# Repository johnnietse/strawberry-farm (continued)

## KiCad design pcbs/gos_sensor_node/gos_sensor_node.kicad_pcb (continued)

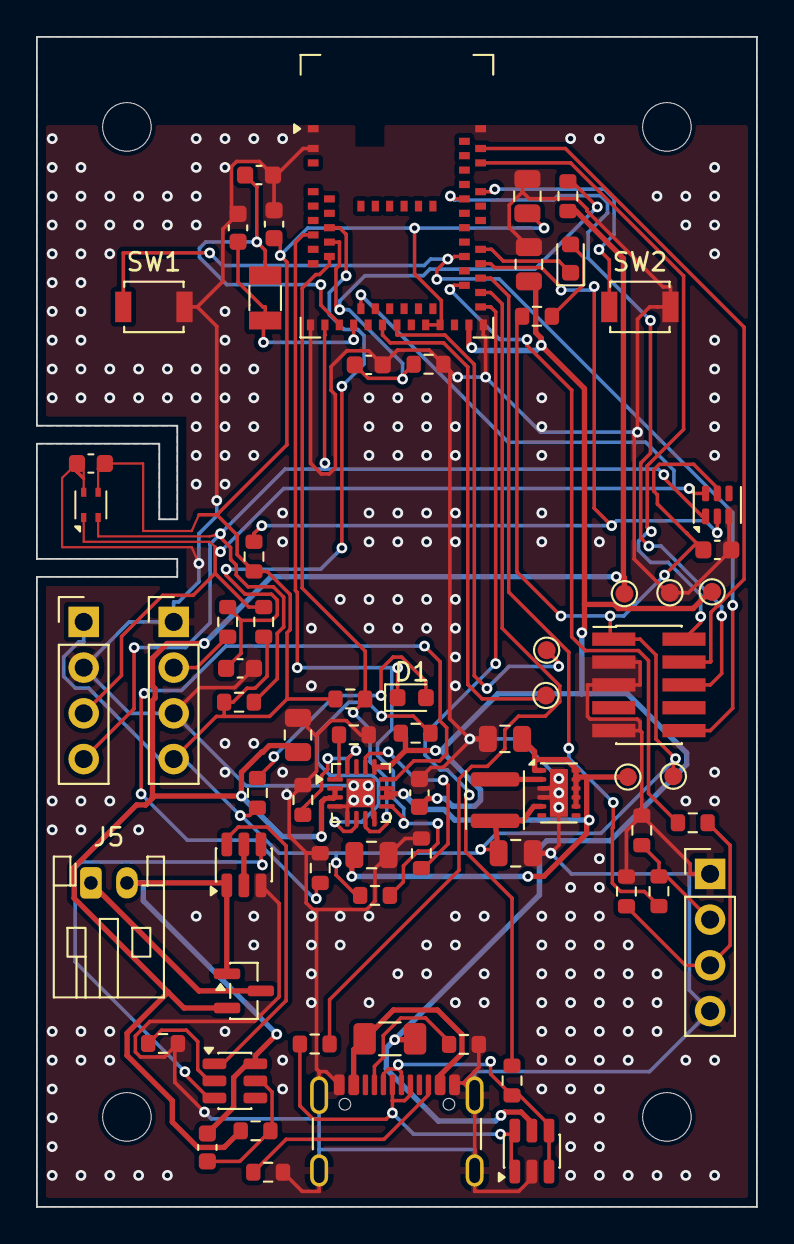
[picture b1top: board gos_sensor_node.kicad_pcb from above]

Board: 4 copper layers, 40.0 x 65.0 mm, 73 parts (0 on the bottom side), 49 nets.

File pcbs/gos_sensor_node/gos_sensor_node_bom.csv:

"Refs","Value","Footprint","LCSC","MPN","Manufacturer","Qty"
"C1,C14","1uF 50V X5R","Capacitor_SMD:C_0603_1608Metric","C15849","CL10A105KB8NNNC","Samsung Electro-Mechanics","2"
"C2,C3,C4,C5,C10,C12","10uF 25V X5R","Capacitor_SMD:C_0805_2012Metric","C15850","CL21A106KAYNNNE","Samsung Electro-Mechanics","6"
"C6,C7,C11,C13","100nF 50V X7R","Capacitor_SMD:C_0603_1608Metric","C14663","CC0603KRX7R9BB104","YAGEO","4"
"C8,C9","12pF C0G","Capacitor_SMD:C_0603_1608Metric","C38523","CL10C120JB8NNNC","Samsung Electro-Mechanics","2"
"D1","LED yellow (charging)","LED_SMD:LED_0603_1608Metric","C2287","KT-0603Y","Hubei KENTO","1"
"D2","LED green (status)","LED_SMD:LED_0603_1608Metric","C12624","KT-0603G","Hubei KENTO","1"
"F1","PTC 0.75A 6V","Fuse:Fuse_1206_3216Metric","C20987","SMD1206P075TF","RUILON","1"
"J1","USB-C USB4105-GF-A","Connector_USB:USB_C_Receptacle_GCT_USB4105-xx-A_16P_TopMnt_Horizontal","C3020560","USB4105-GF-A","GCT","1"
"J2","SWD 2x5 1.27mm","Connector_PinHeader_1.27mm:PinHeader_2x05_P1.27mm_Vertical_SMD","C5155080","FTSH-105-01-L-DV-K","Samtec","1"
"J3","I2C","Connector_PinHeader_2.54mm:PinHeader_1x04_P2.54mm_Vertical","C53055674","254PZ-1x4P-V","LXWCONN","1"
"J4","LED board PWM","Connector_PinHeader_2.54mm:PinHeader_1x04_P2.54mm_Vertical","C53055674","254PZ-1x4P-V","LXWCONN","1"
"J5","Battery JST-PH","Connector_JST:JST_PH_S2B-PH-K_1x02_P2.00mm_Horizontal","C173752","S2B-PH-K-S","JST","1"
"L1","2.2uH","Inductor_SMD:L_APV_ANR3015","C43389","SWPA3015S2R2MT","Sunlord","1"
"Q1","8205A dual NMOS","Package_TO_SOT_SMD:SOT-23-6","C908265","FS8205A","FUXINSEMI","1"
"Q2","AO3401A","Package_TO_SOT_SMD:SOT-23","C15127","AO3401A","Alpha & Omega","1"
"R1,R5,R6,R15,R22,R23","100k","Resistor_SMD:R_0603_1608Metric","C25803","0603WAF1003T5E","UNI-ROYAL","6"
"R2","68k","Resistor_SMD:R_0603_1608Metric","C23231","0603WAF6802T5E","UNI-ROYAL","1"
"R3","3.0k 1%","Resistor_SMD:R_0603_1608Metric","C4211","0603WAF3001T5E","UNI-ROYAL","1"
"R4","1.8k 1%","Resistor_SMD:R_0603_1608Metric","C4177","0603WAF1801T5E","UNI-ROYAL","1"
"R7,R9,R12","1k","Resistor_SMD:R_0603_1608Metric","C21190","0603WAF1001T5E","UNI-ROYAL","3"
"R8,R20,R21","100R","Resistor_SMD:R_0603_1608Metric","C22775","0603WAF1000T5E","UNI-ROYAL","3"
"R10,R11","2.2M 1%","Resistor_SMD:R_0603_1608Metric","C22938","0603WAF2204T5E","UNI-ROYAL","2"
"R13,R14","4.7k","Resistor_SMD:R_0603_1608Metric","C23162","0603WAF4701T5E","UNI-ROYAL","2"
"R16,R17","5.1k","Resistor_SMD:R_0603_1608Metric","C23186","0603WAF5101T5E","UNI-ROYAL","2"
"R18,R19","27R","Resistor_SMD:R_0603_1608Metric","C25190","0603WAF270JT5E","UNI-ROYAL","2"
"SW1","RESET","Button_Switch_SMD:SW_SPST_B3U-1000P","C231329","B3U-1000P","Omron","1"
"SW2","USER","Button_Switch_SMD:SW_SPST_B3U-1000P","C231329","B3U-1000P","Omron","1"
"TH1","NTC 10k","Resistor_SMD:R_0603_1608Metric","C13564","NCP18XH103F03RB","Murata","1"
"U1","BQ24074RGT","Package_DFN_QFN:VQFN-16-1EP_3x3mm_P0.5mm_EP1.6x1.6mm","C54313","BQ24074RGTR","Texas Instruments","1"
"U2","TPS62740DSS","Package_SON:WSON-12-1EP_3x2mm_P0.5mm_EP1x2.65","C128606","TPS62740DSSR","Texas Instruments","1"
"U3","DW01A","Package_TO_SOT_SMD:SOT-23-6","C351410","DW01A","PUOLOP","1"
"U4","MDBT50Q-1MV2","RF_Module:Raytac_MDBT50Q","C5118826","MDBT50Q-1MV2","Raytac","1"
"U5","SHT40-AD1B","Sensor_Humidity:Sensirion_DFN-4_1.5x1.5mm_P0.8mm_SHT4x_NoCentralPad","C2909890","SHT40-AD1B-R2","Sensirion","1"
"U6","TSL25911FN","OptoDevice:AMS_TSL25911FN","C176812","TSL25911FN","ams OSRAM","1"
"U7","USBLC6-2SC6","Package_TO_SOT_SMD:SOT-23-6","C7519","USBLC6-2SC6","STMicroelectronics","1"
"Y1","32.768kHz 9pF","Crystal:Crystal_SMD_3215-2Pin_3.2x1.5mm","C179635","ABS07-32.768KHZ-9-T","Abracon","1"

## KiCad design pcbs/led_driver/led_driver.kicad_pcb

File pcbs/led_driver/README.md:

# G.O.S. LED driver board rev 1.1

Rev 1.1 (2026-11-22) adds a 667 mA option per channel (bridge JP1 / JP2) and a 10 uF capacitor
across each LED string. Rev 1.0 is kept in `pcbs/archive/led_driver_rev1.0/`; the comparison is in
[`documentation/rev3.2_changes.md`](../../documentation/rev3.2_changes.md).

Two constant-current channels for the phytotron grow light, driven by the sensor node's two
PWM outputs (sensor node J4).

The schematic is generated:

```
"C:\Program Files\KiCad\9.0\bin\python.exe" generate_schematic.py --verify
```

`--verify` checks ERC at every severity, the exported netlist against the declared nets, and
that every symbol pin has a footprint pad. Outputs: `led_driver.kicad_sch`,
`led_driver_schematic.pdf`, `led_driver_bom.csv`.

## Board

60 x 45 mm, **4 layers** (F.Cu signals and parts, In1.Cu and In2.Cu solid GND planes, B.Cu
signals; JLCPCB JLC04161H-1080 stack-up, 1.6 mm, ENIG), four M3 holes 4 mm in from the corners.
Generated, then autorouted:

```
"C:\Program Files\KiCad\9.0\bin\python.exe" generate_pcb.py
"C:\Program Files\KiCad\9.0\bin\python.exe" ..\gos_sensor_node\route_pcb.py .
```

`route_pcb.py` needs `FREEROUTING_JAR` (and `JAVA` if the default java is too old); see the sensor
node's `HARDWARE.md`, Board layout. It routes with Freerouting, adds thermal vias in each AL8860
exposed pad, pours GND on all four layers, adds ground stitching vias wherever they fit, runs DRC
with schematic parity and writes `fab/` (Gerbers, drill files, JLCPCB BOM and placement files,
upload zip) and `docs/` (assembly, courtyard, user-layer and all-layer PDFs, renders, STEP model).
Ordering: `documentation/ordering.md`.

The ground planes matter most on this board: two buck converters switch the 24 V supply, and a
plane directly under every switching loop keeps the loop area, and so the radiated noise, small.

Layout: 24 V jack on the left edge; blue channel (U1) in the top half and red (U2) in the bottom;
each channel's diode and inductor in a row from the AL8860 SW pins to its LED terminal on the right
edge; PWM header J2 on the bottom edge. Power nets (VIN, SW, SET, LEDK, GND) are 0.4 mm, signals
0.25 mm.

Current result: DRC at every severity with schematic parity: 0 violations, 0 unconnected, 0 parity
issues.

## Design choices

No requirements were given, so these are engineering defaults. Each one is a constant at the
top of `generate_schematic.py` or a single part to swap.

*Table 1. Design choices for the LED driver and the reason for each.*

| Choice | Value | Why |
|---|---|---|
| Supply | 24 V DC adapter, 5.5 x 2.1 mm centre-positive plug (the jack's centre pin is 2.0 mm) | On 12 V a 3-4 LED blue string needs over 80 % switch duty; the AL8860 is specified for 25 to 75 %. On 24 V both strings sit at roughly 35 to 55 %. |
| Channels | blue 450 nm, red 660 nm | Same spectra as the rev 2 design. |
| LEDs per channel | 4 in series, off-board | About 1 W per LED. Plain FR-4 cannot shed 8 W, so the LEDs go on star (MCPCB) heatsinks wired to J3 and J4. |
| Current | 333 mA per channel as delivered; 667 mA with the jumper bridged (rev 1.1) | AL8860: I = 0.1 V / R_SENSE; 0.30 ohm gives 333 mA (datasheet table). Rev 1.1: bridging JP1 (blue) or JP2 (red) with solder puts R5 / R6 (0.30 ohm) in parallel: 0.15 ohm, 667 mA, below the deep red Rebel's 700 mA DC maximum. Each channel can be set on its own. Suits common 1 W horticulture LEDs. Change R_SENSE for other LEDs (1.0 A max in MSOP-8EP at 0.1 ohm, up to 1.5 A at 0.066 ohm). |
| Inductor | 100 uH (Bourns SRN6045TA-101M) | Datasheet range 33 to 100 uH. Its 47 uH example is for 1 A LEDs; at 333 mA the hysteresis band is a third as wide, and LTspice shows 47 uH switching at up to 1.27 MHz, above the 1 MHz limit, with on-times below the 500 ns needed for 4 % accuracy. 100 uH halves the frequency. Rated 0.92 A against a 0.4 A peak. |
| Dimming | sensor node PWM at 250 Hz into CTRL | Datasheet: CTRL takes 3.3 V logic directly; above 2.5 V = full current, below 0.2 V = off; best accuracy below 500 Hz. |
| LED-string capacitor (rev 1.1) | 10 uF 50 V X7R 1210 across each string (C6, C7) | The AL8860 regulates by hysteresis: the inductor current ramps about +/-15 % around the set value, so at 667 mA it peaks near 775 mA, above the deep red's 700 mA. The capacitor carries the ramp; the LEDs see the average (LTspice, `simulation/led_channel_667mA.cir`). 1 uF was tried first: with only about 0.5 uF left at 12 V bias it still let the LEDs peak at 730 mA. Fitted at both currents; with the string's 1.7 ohm it settles in about 10 us, so 250 Hz PWM is unaffected. |
| Fail-safe | 1.5 kOhm pull-down on each CTRL | A floating CTRL means full brightness. The pull-down keeps the LEDs off when the cable is unplugged or the node is in reset. The datasheet does not give the CTRL pull-up, but its 80 uA maximum shutdown current bounds it: at most 80 uA x 1.5 k = 0.12 V, below the 0.2 V off threshold (LTspice, `simulation/ctrl_failsafe.cir`). 2.2 k left only 24 mV of margin. With the node driving through its 100 ohm resistor, CTRL still reaches 3.0 V (above 2.5 V = full current). |
| Protection | 1.1 A PTC fuse and SS34 series diode on the input | Overload and reversed adapter. The AL8860 has its own open-LED, shorted-LED and over-temperature protection. |

Approximate input power: 333 mA x (4 x 2.75 V blue + 4 x 2.1 V red) = about 6.5 W of LEDs, about
0.3 A from the 24 V adapter (667 mA option: about 14.8 W, 0.7 A worst case, and use a heatsink of
about 1 C/W per channel instead of 2). LTspice puts each channel at 94 to 97 % efficiency. The recommended
adapter (Mean Well GST36U24-P1J, 24 V 1.5 A) has ample margin.

## Recommended LEDs and simulation

Luxeon Star SP-01-V4 (royal blue 448 nm) and SP-01-D2 (deep red 655 nm), each a LUXEON Rebel on a
20 mm star; see `documentation/ordering.md`. With their datasheet forward voltages (typical and
maximum) and a 20 to 28 V supply, LTspice (`simulation/led_channel.cir`) gives 335 to 339 mA per
string, 435 to 672 kHz switching, 32 to 68 % duty and a 392 mA inductor peak: all inside the
AL8860 and inductor limits. Mount the stars on a heatsink and use twisted pair for each string.
Do not plug or unplug an LED string while the board is powered.

## Connectors

*Table 2. Connectors on the LED driver board.*

| Ref | What | Pins |
|---|---|---|
| J1 | 24 V DC jack | centre positive |
| J2 | PWM from sensor node J4, 1x4 2.54 mm | 1 GND, 2 PWM blue, 3 PWM red, 4 GND |
| J3 | blue LED string, 2-pin 3.81 mm terminal | 1 anode (string +), 2 cathode (string -) |
| J4 | red LED string, 2-pin 3.81 mm terminal | 1 anode, 2 cathode |

Both J3 and J4 pins sit near the supply voltage, not near ground: the AL8860 switches the low
side of the string through the inductor. Do not connect either LED pin to ground or to the
enclosure.

## Verified from the Diodes AL8860 datasheet (DS39014 Rev. 8-2, April 2026)

Pinout (MSOP-8EP: SET 1, GND 2-3 and EP, CTRL 4, SW 5-6, N/C 7, VIN 8), 4.5 to 40 V input,
I = 0.1 / R_SENSE, CTRL thresholds and PWM guidance, 33 to 100 uH inductor range, 10 uF X7R
input capacitor close to VIN, 25 to 75 % recommended duty cycle.

## Not verified

- LED forward voltages come from the Luxeon Star product pages (typical and maximum), fitted to a
  simple model; other LEDs need the simulation rerun with their values.
- The Bourns SRN6045TA-101M ratings (1.33 A / 0.92 A, 0.456 ohm) were read from the JLCPCB and Mouser catalogue entries, not from the Bourns datasheet.
- The AL8860 CTRL pull-up is bounded from the datasheet's shutdown current, not measured. Confirm on
  the bench that the LEDs stay dark with J2 unplugged (`documentation/bring_up.md`).
- The switching loops (input capacitor, AL8860, diode, inductor) were placed and routed by hand; the rest is autorouted. No board has been made. Losses per channel are about 0.25 W (switch, diode, inductor, sense resistor), well inside the MSOP-8EP package; not measured.

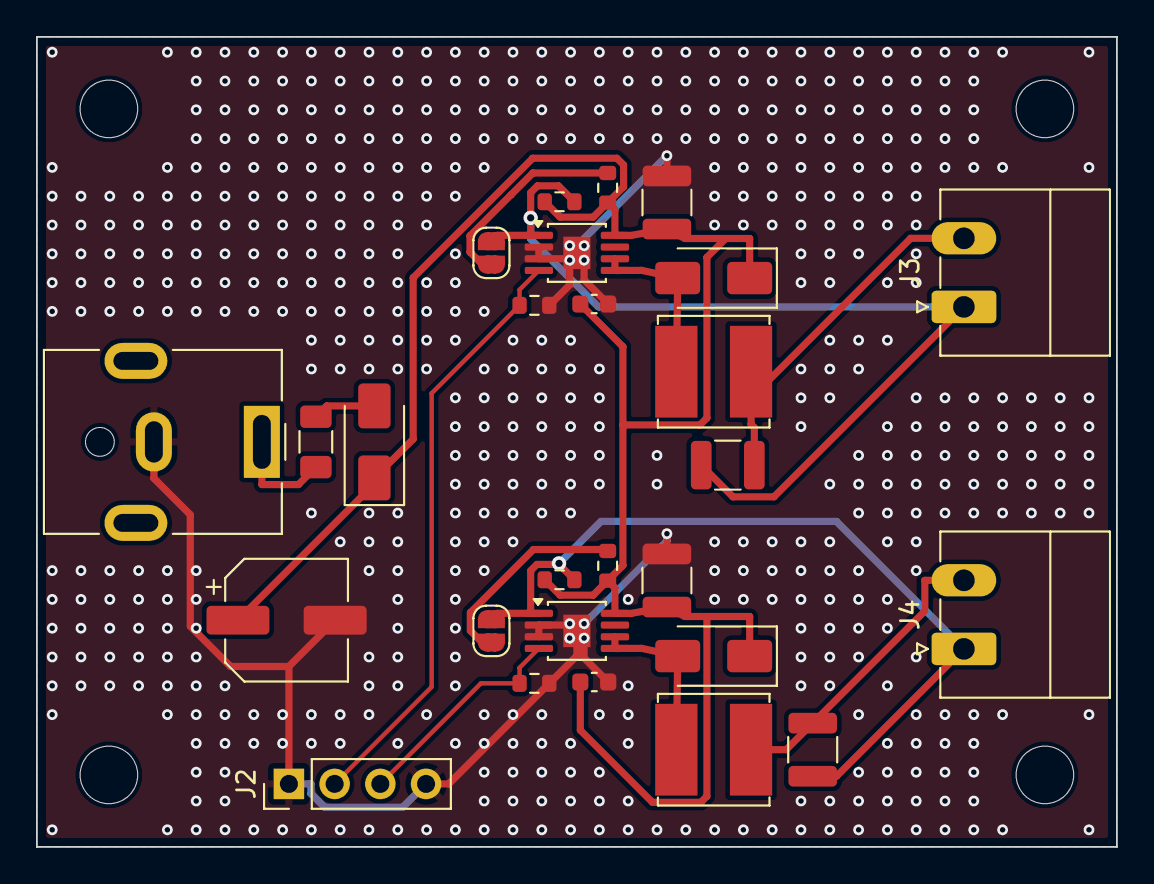
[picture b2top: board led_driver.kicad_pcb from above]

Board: 4 copper layers, 60.0 x 45.0 mm, 31 parts (0 on the bottom side), 14 nets.

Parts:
C1: 47uF 50V; CP_Elec_6.3x7.7
C2, C4, C6, C7: 10uF 50V X7R; C_1210_3225Metric
C3, C5: 100nF 50V X7R; C_0603_1608Metric
D1, D2, D3: SS34; D_SMA
F1: PTC 1.1A 30V; Fuse_1206_3216Metric
H1, H2, H3, H4: M3; MountingHole_3.2mm_M3
J1: 24V DC jack; BarrelJack_CUI_PJ-063AH_Horizontal
J2: PWM from sensor node; PinHeader_1x04_P2.54mm_Vertical
J3: LED blue string; PhoenixContact_MC_1,5_2-G-3.81_1x02_P3.81mm_Horizontal
J4: LED red string; PhoenixContact_MC_1,5_2-G-3.81_1x02_P3.81mm_Horizontal
JP1, JP2: 667 mA; SolderJumper-2_P1.3mm_Open_RoundedPad1.0x1.5mm
L1, L2: 100uH; L_Bourns_SRN6045TA
R1, R3, R5, R6: 0R30 1%; R_0603_1608Metric
R2, R4: 1.5k; R_0603_1608Metric
U1, U2: AL8860MP; MSOP-8-1EP_3x3mm_P0.65mm_EP1.5x1.8mm

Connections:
/CTRL_BLUE: J2.2, R2.1, U1.4
/CTRL_RED: J2.3, R4.1, U2.4
/LEDK_BLUE: C6.2, J3.2, L1.1
/LEDK_RED: C7.2, J4.2, L2.1
/SET_BLUE: C6.1, J3.1, JP1.2, R1.2, U1.1
/SET_BLUE_HI: JP1.1, R5.2
/SET_RED: C7.1, J4.1, JP2.2, R3.2, U2.1
/SET_RED_HI: JP2.1, R6.2
/SW_BLUE: D2.2, L1.2, U1.5, U1.6
/SW_RED: D3.2, L2.2, U2.5, U2.6
/VIN: C1.1, C2.1, C3.1, C4.1, C5.1, D1.1, D2.1, D3.1, R1.1, R3.1, R5.1, R6.1, U1.8, U2.8
/VIN_FUSED: D1.2, F1.2
/VIN_JACK: F1.1, J1.1
GND: C1.2, C2.2, C3.2, C4.2, C5.2, J1.2, J2.1, J2.4, R2.2, R4.2, U1.2, U1.3, U1.9, U2.2, U2.3, U2.9

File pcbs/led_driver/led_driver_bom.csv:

"Refs","Value","Footprint","LCSC","MPN","Manufacturer","Qty"
"C1","47uF 50V","Capacitor_SMD:CP_Elec_6.3x7.7","C72523","RVT1H470M0607","ROQANG","1"
"C2,C4","10uF 50V X7R","Capacitor_SMD:C_1210_3225Metric","C138687","CL32B106KBJNNNE","Samsung Electro-Mechanics","2"
"C3,C5","100nF 50V X7R","Capacitor_SMD:C_0603_1608Metric","C14663","CC0603KRX7R9BB104","YAGEO","2"
"D1,D2,D3","SS34","Diode_SMD:D_SMA","C8678","SS34","MDD (Microdiode)","3"
"F1","PTC 1.1A 30V","Fuse:Fuse_1206_3216Metric","C21714343","BSMD1206-110-30V","BHFUSE","1"
"J1","24V DC jack","Connector_BarrelJack:BarrelJack_CUI_PJ-063AH_Horizontal","C22434582","PJ-063AH","CUI Devices","1"
"J2","PWM from sensor node","Connector_PinHeader_2.54mm:PinHeader_1x04_P2.54mm_Vertical","C53055674","254PZ-1x4P-V","LXWCONN","1"
"J3","LED blue string","Connector_Phoenix_MC:PhoenixContact_MC_1,5_2-G-3.81_1x02_P3.81mm_Horizontal","C480537","1803277","Phoenix Contact","1"
"J4","LED red string","Connector_Phoenix_MC:PhoenixContact_MC_1,5_2-G-3.81_1x02_P3.81mm_Horizontal","C480537","1803277","Phoenix Contact","1"
"L1,L2","100uH","Inductor_SMD:L_Bourns_SRN6045TA","C3222641","SRN6045TA-101M","Bourns","2"
"R1,R3","0R30 1%","Resistor_SMD:R_0603_1608Metric","C309621","RL0603FR-070R3L","YAGEO","2"
"R2,R4","1.5k","Resistor_SMD:R_0603_1608Metric","C22843","0603WAF1501T5E","UNI-ROYAL","2"
"U1,U2","AL8860MP","Package_SO:MSOP-8-1EP_3x3mm_P0.65mm_EP1.5x1.8mm","C500782","AL8860MP-13","Diodes Incorporated","2"

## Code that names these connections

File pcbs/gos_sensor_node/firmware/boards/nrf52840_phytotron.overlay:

/ {
	chosen {
		zephyr,console = &uart0;
		zephyr,shell-uart = &uart0;
		zephyr,bt-c2h-uart = &uart0;
		zephyr,bt-hci-uart = &uart0;
		zephyr,bt-mon-uart = &uart0;
	};

	aliases {
		led0 = &led_blue;
		led1 = &led_red;
		sw0 = &button_reset;
		sw1 = &button_dfu;
		i2c0 = &i2c0;
		i2c1 = &i2c1;
		spi0 = &spi0;
		spi1 = &spi1;
		uart0 = &uart0;
		uart1 = &uart1;
		pwm0 = &pwm0;
		pwm1 = &pwm1;
		adc0 = &adc;
		ieee802154 = &ieee802154;
	};

	/* Battery ADC Channels */
	adc: adc {
		compatible = "nordic,nrf-saadc";
		status = "okay";
		#address-cells = <1>;
		#size-cells = <0>;

		channel@0 {
			reg = <0>;
			zephyr,gain = "ADC_GAIN_1_6";
			zephyr,reference = "ADC_REF_INTERNAL";
			zephyr,acquisition-time = <ADC_ACQ_TIME(ADC_ACQ_TIME_MICROSECONDS, 3)>;
			zephyr,channel-id = <0>;
			zephyr,input-positive = <28>; /* P0.28 = AIN4 = VBATT_SENSE */
		};

		channel@1 {
			reg = <1>;
			zephyr,gain = "ADC_GAIN_1_6";
			zephyr,reference = "ADC_REF_INTERNAL";
			zephyr,acquisition-time = <ADC_ACQ_TIME(ADC_ACQ_TIME_MICROSECONDS, 3)>;
			zephyr,channel-id = <1>;
			zephyr,input-positive = <30>; /* P0.30 = AIN6 = VBUS_SENSE */
		};

		channel@2 {
			reg = <2>;
			zephyr,gain = "ADC_GAIN_1_6";
			zephyr,reference = "ADC_REF_INTERNAL";
			zephyr,acquisition-time = <ADC_ACQ_TIME(ADC_ACQ_TIME_MICROSECONDS, 3)>;
			zephyr,channel-id = <2>;
			zephyr,input-positive = <31>; /* P0.31 = AIN7 = VSYS_SENSE */
		};
	};

	/* Battery ADC Channels */
	battery_adc: battery_adc {
		compatible = "gos,battery-adc";
		io-channels = <&adc 0>, <&adc 1>, <&adc 2>;
		io-channel-names = "vbatt", "vbus", "vsys";
		status = "okay";
	};

	/* External SPI Flash for LittleFS */
	ext_flash: ext_flash {
		compatible = "jedec,spi-nor";
		reg = <0>;
		spi-max-frequency = <8000000>;
		label = "EXT_FLASH";
		jedec-id = [ef 40 15]; /* W25Q16JV */
		size = <2097152>; /* 2MB */
		has-dpd;
		t-enter-dpd = <10000>;
		t-exit-dpd = <35000>;
		status = "okay";
	};

	/* BQ24075 Charger */
	bq24075: bq24075@6b {
		compatible = "ti,bq24075";
		reg = <0x6b>;
		status = "okay";
		interrupt-parent = <&gpio0>;
		interrupts = <8 IRQ_TYPE_LEVEL_LOW>; /* PGOOD pin */
		ti,charge-current-ma = <742>;
		ti,input-current-limit-ma = <500>;
		ti,precharge-current-ma = <74>;
		ti,termination-current-ma = <74>;
		ti,voltage-regulation-mv = <4200>;
		ti,precharge-voltage-mv = <3000>;
		ti,recharge-threshold-mv = <100>;
		ti,watchdog-timeout-s = <7200>;
		ti,enable-charger;
		ti,enable-watchdog;
	};

	/* TPS62740 Buck Converter */
	tps62740: tps62740@0 {
		compatible = "ti,tps62740";
		reg = <0>;
		status = "okay";
		gpios = <&gpio0 15 GPIO_ACTIVE_HIGH>, /* EN */
		        <&gpio0 16 GPIO_ACTIVE_HIGH>, /* VSEL0 */
		        <&gpio0 17 GPIO_ACTIVE_HIGH>; /* VSEL1 */
		interrupt-parent = <&gpio0>;
		interrupts = <18 IRQ_TYPE_LEVEL_LOW>; /* PG pin */
		ti,vsel0-gpio = <&gpio0 16 GPIO_ACTIVE_HIGH>;
		ti,vsel1-gpio = <&gpio0 17 GPIO_ACTIVE_HIGH>;
		ti,enable-gpio = <&gpio0 15 GPIO_ACTIVE_HIGH>;
		ti,pg-gpio = <&gpio0 18 GPIO_ACTIVE_LOW>;
	};

	/* DW01A Protection IC */
	dw01a: dw01a@0 {
		compatible = "ablic,dw01a";
		status = "okay";
		interrupt-parent = <&gpio0>;
		interrupts = <19 IRQ_TYPE_LEVEL_LOW>, /* OD pin */
		             <20 IRQ_TYPE_LEVEL_LOW>; /* OC pin */
		gpios = <&gpio0 21 GPIO_ACTIVE_HIGH>, /* OD output */
		        <&gpio0 22 GPIO_ACTIVE_HIGH>, /* OC output */
		        <&gpio0 23 GPIO_ACTIVE_HIGH>; /* CS input */
		ablic,ov-threshold-mv = <4250>;
		ablic,uv-threshold-mv = <2400>;
		ablic,oc-threshold-mv = <150>;
		ablic,oc-delay-ms = <100>;
	};

	/* FS8205A Dual N-MOSFET */
	fs8205a: fs8205a@0 {
		compatible = "fairchild,fs8205a";
		status = "okay";
		gpios = <&gpio0 24 GPIO_ACTIVE_HIGH>, /* Q1 gate */
		        <&gpio0 25 GPIO_ACTIVE_HIGH>; /* Q2 gate */
	};

	/* SX1262 LoRa Transceiver */
	sx1262: sx1262@0 {
		compatible = "semtech,sx1262";
		reg = <0>;
		status = "okay";
		spi-max-frequency = <8000000>;
		spi-cpol = <0>;
		spi-cpha = <0>;
		spi-hold-cs-delay = <10>;
		spi-cs-gpios = <&gpio0 10 GPIO_ACTIVE_LOW>; /* NSS */
		interrupt-parent = <&gpio0>;
		interrupts = <11 IRQ_TYPE_LEVEL_HIGH>,  /* BUSY */
		             <12 IRQ_TYPE_LEVEL_HIGH>,  /* DIO1 */
		             <13 IRQ_TYPE_LEVEL_HIGH>,  /* DIO2 */
		             <13 IRQ_TYPE_LEVEL_HIGH>;  /* DIO3 */
		reset-gpios = <&gpio0 14 GPIO_ACTIVE_LOW>; /* NRESET */
		semtech,tx-power = <22>;
		semtech,frequency = <915000000>;
		semtech,spreading-factor = <7>;
		semtech,bandwidth = <125000>;
		semtech,coding-rate = <1>;
		semtech,preamble-length = <8>;
		semtech,tx-power-dbm = <22>;
		semtech,rf-switch = <0>; /* RFO */
	};

	/* L76K GNSS Module */
	l76k: l76k@0 {
		compatible = "quectel,l76k";
		status = "okay";
		reg = <0>;
		spi-max-frequency = <1000000>;
		spi-cpol = <0>;
		spi-cpha = <0>;
		spi-hold-cs-delay = <10>;
		spi-cs-gpios = <&gpio0 15 GPIO_ACTIVE_LOW>;
		interrupt-parent = <&gpio0>;
		interrupts = <16 IRQ_TYPE_LEVEL_HIGH>; /* PPS */
		reset-gpios = <&gpio0 16 GPIO_ACTIVE_LOW>;
		quectel,baudrate = <9600>;
		quectel,pps-gpio = <&gpio0 16 GPIO_ACTIVE_HIGH>;
	};

	/* AL8860 LED Drivers */
	al8860_blue: al8860_blue@0 {
		compatible = "diodes,al8860";
		status = "okay";
		reg = <0>;
		gpios = <&gpio0 13 GPIO_ACTIVE_HIGH>, /* EN/PWM */
		        <&gpio0 14 GPIO_ACTIVE_HIGH>; /* FB */
		diodes,current-ma = <300>;
		diodes,pwm-frequency = <100000>;
		diodes,bootstrap-capacitor = <10>;
	};

	al8860_red: al8860_red@0 {
		compatible = "diodes,al8860";
		status = "okay";
		reg = <0>;
		gpios = <&gpio0 18 GPIO_ACTIVE_HIGH>, /* EN/PWM */
		        <&gpio0 19 GPIO_ACTIVE_HIGH>; /* FB */
		diodes,current-ma = <300>;
		diodes,pwm-frequency = <100000>;
		diodes,bootstrap-capacitor = <10>;
	};

	/* External SPI Flash for LittleFS */
	ext_flash: ext_flash {
		compatible = "jedec,spi-nor";
		reg = <0>;
		spi-max-frequency = <8000000>;
		label = "EXT_FLASH";
		jedec-id = [ef 40 15]; /* W25Q16JV */
		size = <2097152>; /* 2MB */
		has-dpd;
		t-enter-dpd = <10000>;
		t-exit-dpd = <35000>;
		status = "okay";
	};
};

&gpio0 {
	status = "okay";
};

&gpio1 {
	status = "okay";
};

&i2c0 {
	status = "okay";
	clock-frequency = <100000>;
	sda-pin = <26>;
	scl-pin = <27>;

	sht40: sht40@44 {
		compatible = "sensirion,sht40";
		reg = <0x44>;
		status = "okay";
		sensirion,heater = <0>;
	};

	tsl2591: tsl2591@29 {
		compatible = "ams,tsl2591";
		reg = <0x29>;
		status = "okay";
		interrupt-parent = <&gpio0>;
		interrupts = <15 IRQ_TYPE_LEVEL_LOW>; /* INT pin */
		ams,integration-time = <0x00>; /* 100ms */
		ams,gain = <0x10>; /* 25x */
	};

	/* External I2C Expansion Header */
	i2c_expansion: i2c_expansion@0 {
		compatible = "i2c-expansion";
		reg = <0>;
		status = "okay";
	};
};

&i2c1 {
	status = "okay";
	clock-frequency = <100000>;
	sda-pin = <30>;
	scl-pin = <31>;
};

&spi0 {
	status = "okay";
	sck-pin = <10>;
	miso-pin = <11>;
	mosi-pin = <12>;
	cs-gpios = <&gpio0 10 GPIO_ACTIVE_LOW>;
};

&spi1 {
	status = "okay";
	sck-pin = <16>;
	miso-pin = <17>;
	mosi-pin = <18>;
	cs-gpios = <&gpio0 15 GPIO_ACTIVE_LOW>;
};

&uart0 {
	status = "okay";
	current-speed = <115200>;
	tx-pin = <6>;
	rx-pin = <8>;
	rts-pin = <7>;
	cts-pin = <5>;
};

&uart1 {
	status = "okay";
	current-speed = <9600>;
	tx-pin = <20>;
	rx-pin = <21>;
};

&pwm0 {
	status = "okay";
	ch0-pin = <13>; /* PWM_BLUE */
	ch1-pin = <14>; /* PWM_RED */
	ch2-pin = <18>; /* SWDIO */
	ch3-pin = <19>; /* SWCLK */
};

&adc {
	status = "okay";
};

&ieee802154 {
	status = "okay";
};

&pwm0 {
	status = "okay";
	ch0-pin = <13>; /* PWM_BLUE */
	ch1-pin = <14>; /* PWM_RED */
};

&adc {
	status = "okay";
};

&wdt {
	status = "okay";
	timeout = <30000>;
};

&flash0 {
	partitions {
		compatible = "fixed-partitions";
		#address-cells = <1>;
		#size-cells = <1>;

		boot_partition: partition@0 {
			label = "mcuboot";
			reg = <0x00000000 0x00010000>;
			read-only;
		};

		slot0_partition: partition@10000 {
			label = "image-0";
			reg = <0x00010000 0x00060000>;
		};

		slot1_partition: partition@70000 {
			label = "image-1";
			reg = <0x00070000 0x00060000>;
		};

		scratch_partition: partition@d0000 {
			label = "scratch";
			reg = <0x000d0000 0x00010000>;
		};

		storage_partition: partition@e0000 {
			label = "storage";
			reg = <0x000e0000 0x00020000>;
		};
	};
};

&nvs {
	partition = <&storage_partition>;
};

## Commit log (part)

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2026-02-08 Initial commit: G.O.S. Phenotyping Platform v1.0
2026-02-08 docs: Expand interview prep script to 6879 lines with comprehensive file-by-file reference guide
2026-02-08 docs: Update README
2026-02-08 docs: Fix corrupted interview prep script with clean UTF-8 encoding
2026-02-15 docs: Add PCB layout preparation checklist for KiCad
2026-02-15 docs: Add PCB design AI prompt templates for hardware engineering
2026-02-15 docs: Expand PCB design reference with detailed engineering formulas, protection circuits, and stackup design
2026-02-15 docs: Add comprehensive G.O.S. PCB design specification with BOM, schematics, and layout strategy
2026-02-15 Update README to remove advisor details
    Removed project advisor information from README.
2026-02-17 v2.0: Redesign PCB spec with complete BOM, ESD protection, BQ24075 charger, and engineering insights
2026-02-17 fix: Resolve all critical/moderate issues from PCB spec validity audit
    - C1: nRF52840 package corrected from QFN-48 to aQFN-73
    - C2: AL8860 VIN warning added - must use LED_VIN (4.5V min), not VDD_3V3
    - C3: TPS62740 VSEL truth table added (all HIGH = 3.3V)
    - M1: Battery divider redesigned with P-MOSFET gate (zero standby drain)
    - M2: 32.768kHz crystal caps reverted to 6.8pF (Cstray~4pF per Nordic)
    - M3: nRF52840 thermal via pattern added (4x4 grid, 0.3mm drill)
2026-02-17 fix: Complete PCB doc validation — add missing BOM entries, fix bench_testing, correct block diagram
    - Added R1/R2 (1MOhm), Q4 (DMG2305UX), R30 (100kOhm), C33 (100nF) to BOM
    - Corrected block diagram: Boost -> Buck (TPS62740 is a buck converter)
    - Updated component count: ~70 line items, ~108 placed components
    - bench_testing.md: LDO -> TPS62740 buck regulator, 1.8V -> 1.3V at DEC4
2026-02-17 sync: Propagate PCB v2.0 changes to all affected project files
    - overlay: battery divider 100kOhm -> 1MOhm (gated via Q4 P-MOSFET)
    - power_mgmt.h: battery range 3.3V -> 3.0V (18650), discharge curve updated
    - hardware_specs.md: complete rewrite with correct BOM, charger, protection, power budget
    - nrf52840_pinout.md: added AIN0, P0.03 BAT_EN, TSL2591 INT, USB-C, SWD pins
2026-02-17 fix(pcb-spec): 12 datasheet-verified corrections to PCB design spec and docs
    PCB Design Specification (11 fixes):
    - BQ24075 ISET R8: 2kohm->1.2kohm (KISET=890, actual 742mA not 750mA)
    - RF matching: L2=10nH->L4=3.9nH per Nordic AN-032, C31=0.8pF ref added
    - Overlay quote: 100kohm->1Mohm to match actual gated divider
    - SHT4x cap ref: C11->C23 to match BOM table
    - DW01A ODP threshold: 2.5V->2.4V per DW01A datasheet
2026-02-17 fix: project-wide sync against PCB spec v2.0
    mechanical/enclosure_gen.scad:
    - PCB dims: 64x100mm (DK) -> 40x65mm (custom G.O.S. PCB per spec 12.1)
    - Header: DK/Dongle -> Custom G.O.S. PCB (nRF52840 aQFN-73)
    gateway/services/farm_sim.py:
    - Battery sim min clamp: 3200mV -> 3000mV (18650 useful floor)
    ml_engine/phenotyping.py:
